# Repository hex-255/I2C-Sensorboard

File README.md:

# I2C-Sensorboard
Arduino Clone with multitude of I2C Sensors on-board meant as a learning platform for embedded programming

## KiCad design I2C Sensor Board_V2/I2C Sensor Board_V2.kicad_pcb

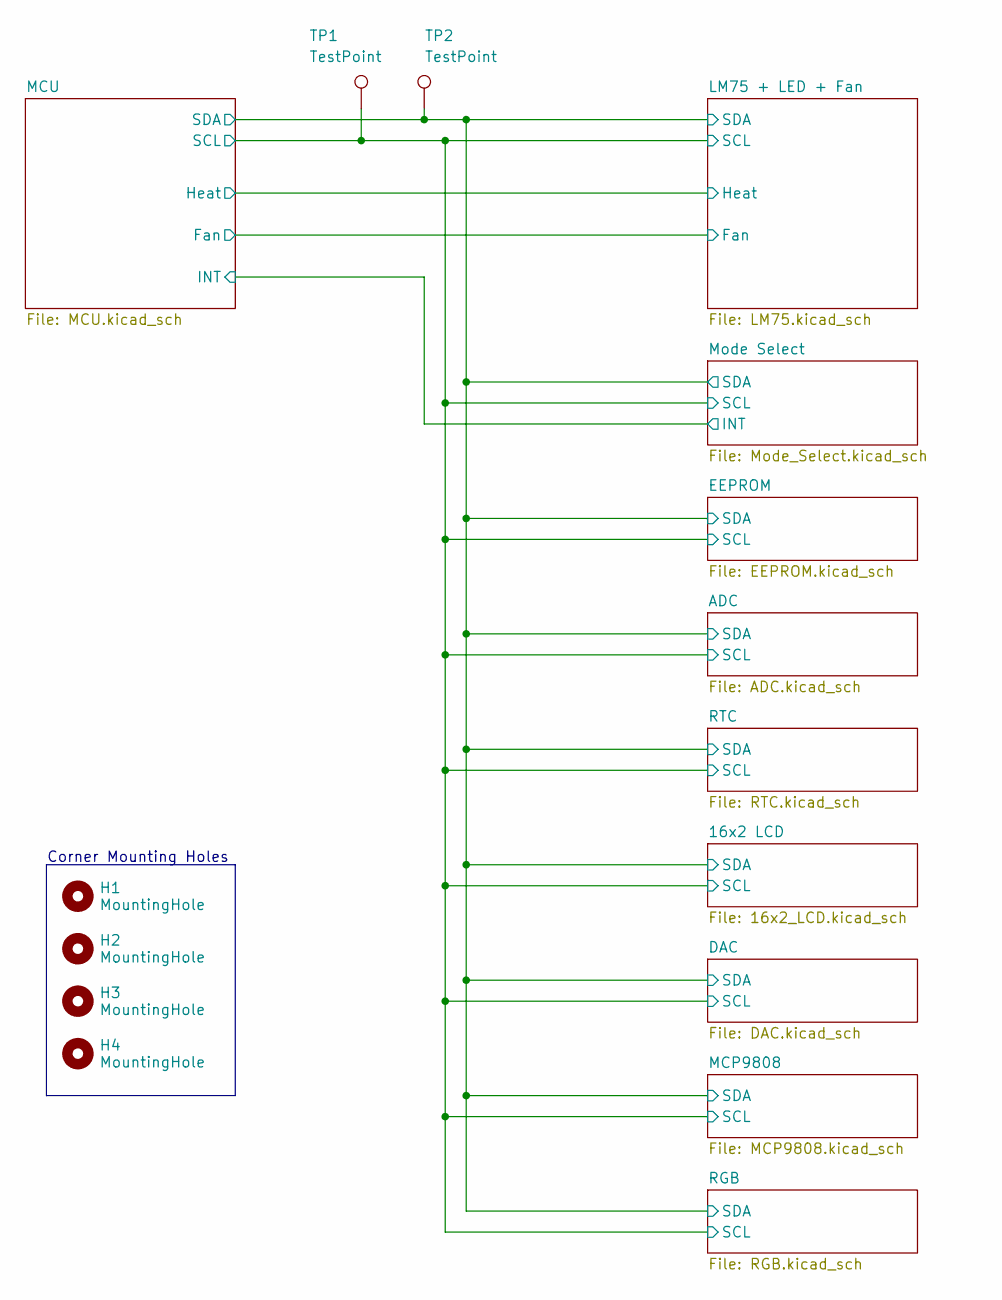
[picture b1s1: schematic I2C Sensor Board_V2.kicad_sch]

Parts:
H1, H2, H3, H4: MountingHole; MountingHole_3.2mm_M3_DIN965_Pad
TP1, TP2: TestPoint; Testpoint_5019_HandSolder

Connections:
/MCU/SCL: TP1.1 (1_1); also elsewhere on the board
/MCU/SDA: TP2.1 (1_1); also elsewhere on the board

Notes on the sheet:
Corner Mounting Holes

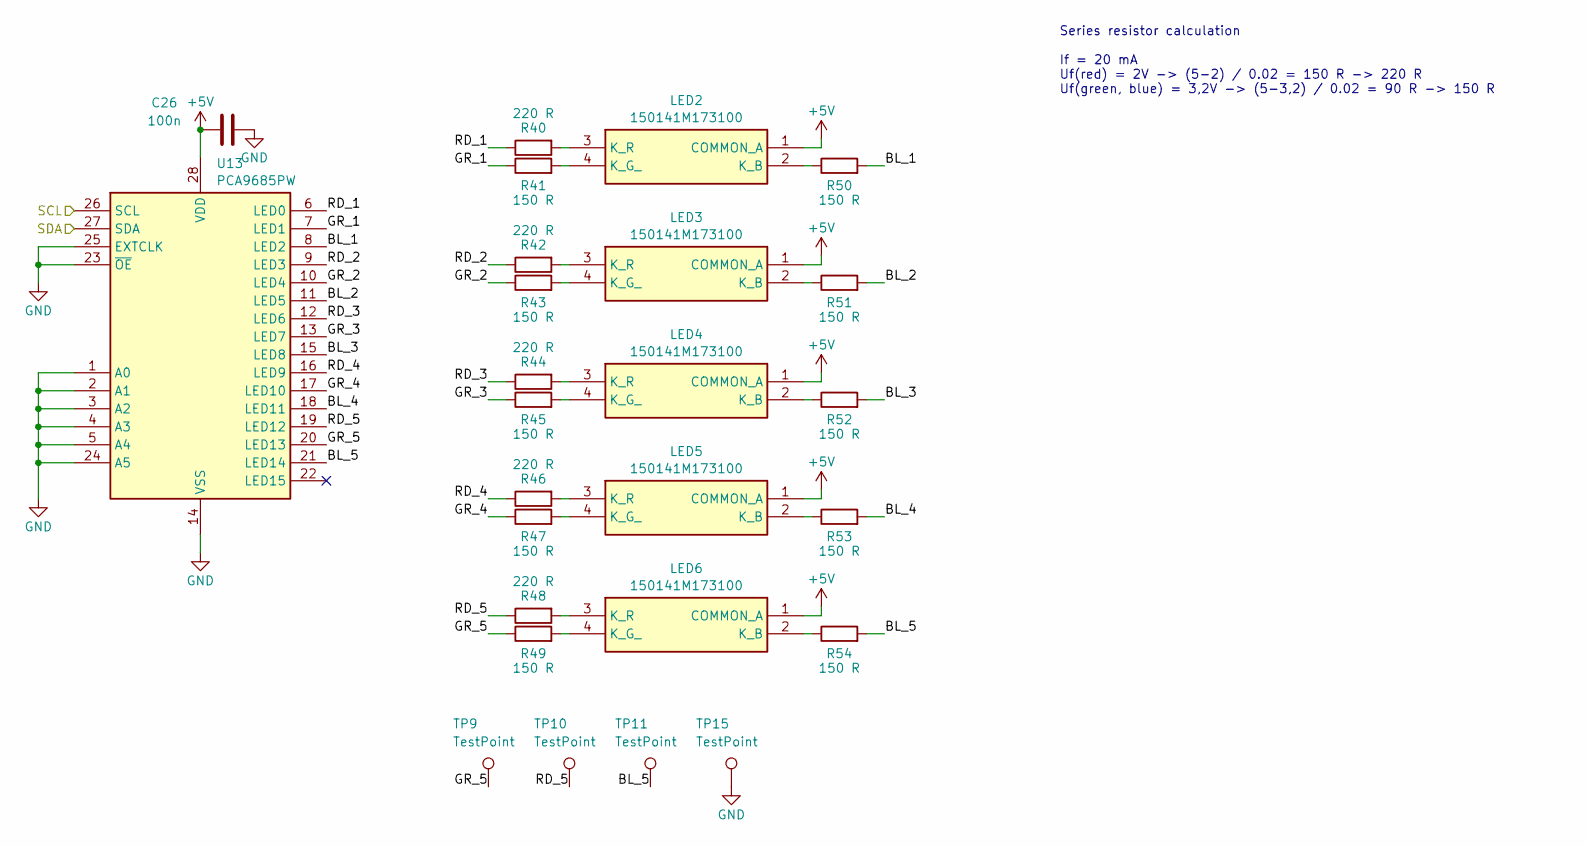
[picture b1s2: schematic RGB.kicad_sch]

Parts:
C26: 100n; C_0805_2012Metric_Pad1.18x1.45mm_HandSolder
LED2, LED3, LED4, LED5, LED6: 150141M173100; Manufacturer_Part_Number 150141M173100; Mouser Part Number 710-150141M173100
R40, R42, R44, R46, R48: 220 R; R_0805_2012Metric_Pad1.20x1.40mm_HandSolder
R41, R43, R45, R47, R49, R50, R51, R52, R53, R54: 150 R; R_0805_2012Metric_Pad1.20x1.40mm_HandSolder
TP9, TP10, TP11, TP15: TestPoint; Testpoint_5019_HandSolder
U13: PCA9685PW; TSSOP-28_4.4x9.7mm_P0.65mm

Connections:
+5V: C26.1, LED2.1 (COMMON_A), LED3.1 (COMMON_A), LED4.1 (COMMON_A), LED5.1 (COMMON_A), LED6.1 (COMMON_A), U13.28 (VDD); also elsewhere on the board
/MCU/SCL: U13.26 (SCL); also elsewhere on the board
/MCU/SDA: U13.27 (SDA); also elsewhere on the board
/RGB/BL_1: R50.2, U13.8 (LED2)
/RGB/BL_2: R51.2, U13.11 (LED5)
/RGB/BL_3: R52.2, U13.15 (LED8)
/RGB/BL_4: R53.2, U13.18 (LED11)
/RGB/BL_5: R54.2, TP11.1 (1_1), U13.21 (LED14)
/RGB/GR_1: R41.1, U13.7 (LED1)
/RGB/GR_2: R43.1, U13.10 (LED4)
/RGB/GR_3: R45.1, U13.13 (LED7)
/RGB/GR_4: R47.1, U13.17 (LED10)
/RGB/GR_5: R49.1, TP9.1 (1_1), U13.20 (LED13)
/RGB/RD_1: R40.1, U13.6 (LED0)
/RGB/RD_2: R42.1, U13.9 (LED3)
/RGB/RD_3: R44.1, U13.12 (LED6)
/RGB/RD_4: R46.1, U13.16 (LED9)
/RGB/RD_5: R48.1, TP10.1 (1_1), U13.19 (LED12)
GND: C26.2, TP15.1, U13.1 (A0), U13.2 (A1), U13.3 (A2), U13.4 (A3), U13.5 (A4), U13.14 (VSS), U13.23 (~OE), U13.24 (A5), U13.25 (EXTCLK); also elsewhere on the board
unnamed: LED2.2 (K_B), R50.1
unnamed: LED2.4 (K_G_), R41.2
unnamed: LED2.3 (K_R), R40.2
unnamed: LED3.2 (K_B), R51.1
unnamed: LED3.4 (K_G_), R43.2
unnamed: LED3.3 (K_R), R42.2
unnamed: LED4.2 (K_B), R52.1
unnamed: LED4.4 (K_G_), R45.2
unnamed: LED4.3 (K_R), R44.2
unnamed: LED5.2 (K_B), R53.1
unnamed: LED5.4 (K_G_), R47.2
unnamed: LED5.3 (K_R), R46.2
unnamed: LED6.2 (K_B), R54.1
unnamed: LED6.4 (K_G_), R49.2
unnamed: LED6.3 (K_R), R48.2

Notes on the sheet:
Series resistor calculation If = 20 mA Uf(red) = 2V -> (5-2) / 0.02 = 150 R -> 220 R Uf(green, blue) = 3,2V -> (5-3,2) / 0.02 = 90 R -> 150 R

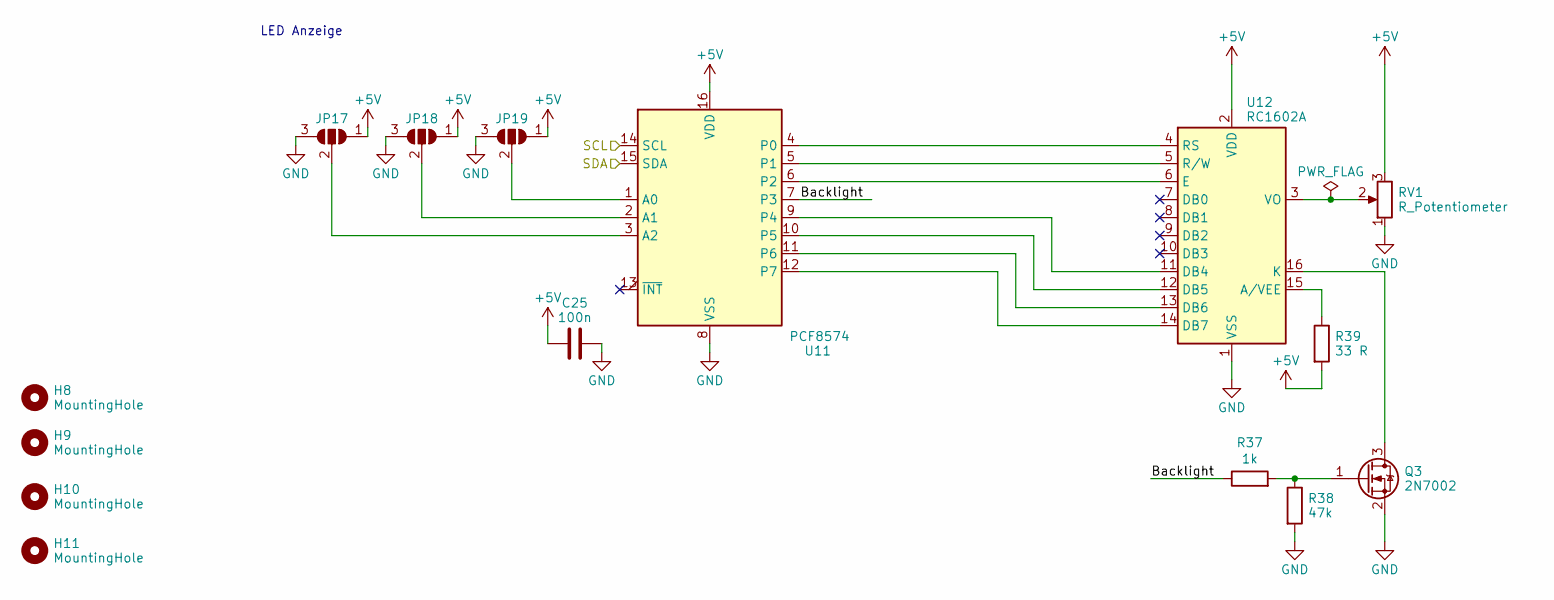
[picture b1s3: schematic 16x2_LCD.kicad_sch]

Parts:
C25: 100n; C_0805_2012Metric_Pad1.18x1.45mm_HandSolder
H8, H9, H10, H11: MountingHole; MountingHole_3.2mm_M3_DIN965_Pad
JP17, JP18, JP19: SolderJumper_3_Open; SolderJumper-3_P1.3mm_Open_Pad1.0x1.5mm_NumberLabels
Q3: 2N7002; SOT-23
R37: 1k; R_0805_2012Metric_Pad1.20x1.40mm_HandSolder
R38: 47k; R_0805_2012Metric_Pad1.20x1.40mm_HandSolder
R39: 33 R; R_0805_2012Metric_Pad1.20x1.40mm_HandSolder
RV1: R_Potentiometer; TRIM_TC33X-2-103E
U11: PCF8574; SOIC-16W_7.5x10.3mm_P1.27mm
U12: RC1602A; PinSocket_1x16_P2.54mm_Vertical

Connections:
+5V: C25.1, JP17.1 (A), JP18.1 (A), JP19.1 (A), R39.2, RV1.3, U11.16 (VDD), U12.2 (VDD); also elsewhere on the board
/16x2 LCD/Backlight: R37.1, U11.7 (P3)
/MCU/SCL: U11.14 (SCL); also elsewhere on the board
/MCU/SDA: U11.15 (SDA); also elsewhere on the board
GND: C25.2, JP17.3 (B), JP18.3 (B), JP19.3 (B), Q3.2 (S), R38.2, RV1.1, U11.8 (VSS), U12.1 (VSS); also elsewhere on the board
unnamed: JP17.2 (C), U11.3 (A2)
unnamed: JP18.2 (C), U11.2 (A1)
unnamed: JP19.2 (C), U11.1 (A0)
unnamed: Q3.3 (D), U12.16 (K)
unnamed: Q3.1 (G), R37.2, R38.1
unnamed: U11.4 (P0), U12.4 (RS)
unnamed: U11.5 (P1), U12.5 (R/W)
unnamed: U11.6 (P2), U12.6 (E)
unnamed: U11.9 (P4), U12.11 (DB4)
unnamed: U11.10 (P5), U12.12 (DB5)
unnamed: U11.11 (P6), U12.13 (DB6)
unnamed: U11.12 (P7), U12.14 (DB7)
unnamed: R39.1, U12.15 (A/VEE)
unnamed: RV1.2, U12.3 (VO)

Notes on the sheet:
LED Anzeige

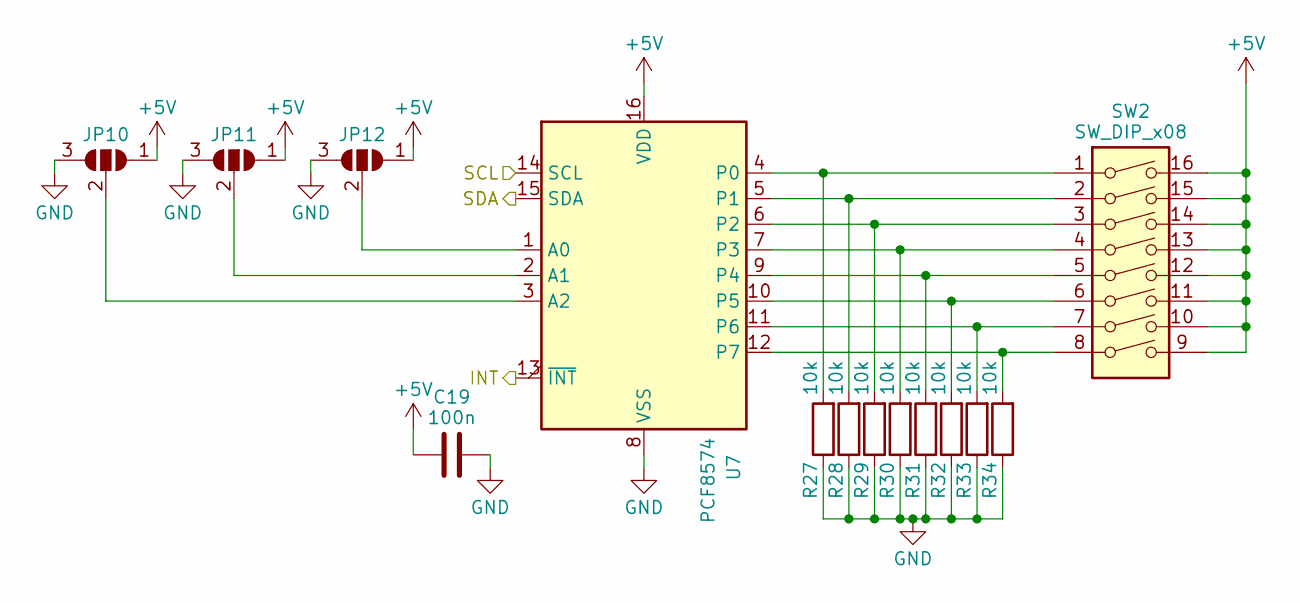
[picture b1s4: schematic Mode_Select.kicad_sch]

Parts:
C19: 100n; C_0805_2012Metric_Pad1.18x1.45mm_HandSolder
JP10, JP11, JP12: SolderJumper_3_Open; SolderJumper-3_P1.3mm_Open_Pad1.0x1.5mm_NumberLabels
R27, R28, R29, R30, R31, R32, R33, R34: 10k; R_0805_2012Metric_Pad1.20x1.40mm_HandSolder
SW2: SW_DIP_x08; SW_DIP_SPSTx08_Slide_9.78x22.5mm_W8.61mm_P2.54mm
U7: PCF8574; SOIC-16W_7.5x10.3mm_P1.27mm

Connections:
+5V: C19.1, JP10.1 (A), JP11.1 (A), JP12.1 (A), SW2.9, SW2.10, SW2.11, SW2.12, SW2.13, SW2.14, SW2.15, SW2.16, U7.16 (VDD); also elsewhere on the board
/MCU/INT: U7.13 (~INT); also elsewhere on the board
/MCU/SCL: U7.14 (SCL); also elsewhere on the board
/MCU/SDA: U7.15 (SDA); also elsewhere on the board
GND: C19.2, JP10.3 (B), JP11.3 (B), JP12.3 (B), R27.1, R28.1, R29.1, R30.1, R31.1, R32.1, R33.1, R34.1, U7.8 (VSS); also elsewhere on the board
unnamed: JP10.2 (C), U7.3 (A2)
unnamed: JP11.2 (C), U7.2 (A1)
unnamed: JP12.2 (C), U7.1 (A0)
unnamed: R27.2, SW2.1, U7.4 (P0)
unnamed: R28.2, SW2.2, U7.5 (P1)
unnamed: R29.2, SW2.3, U7.6 (P2)
unnamed: R30.2, SW2.4, U7.7 (P3)
unnamed: R31.2, SW2.5, U7.9 (P4)
unnamed: R32.2, SW2.6, U7.10 (P5)
unnamed: R33.2, SW2.7, U7.11 (P6)
unnamed: R34.2, SW2.8, U7.12 (P7)

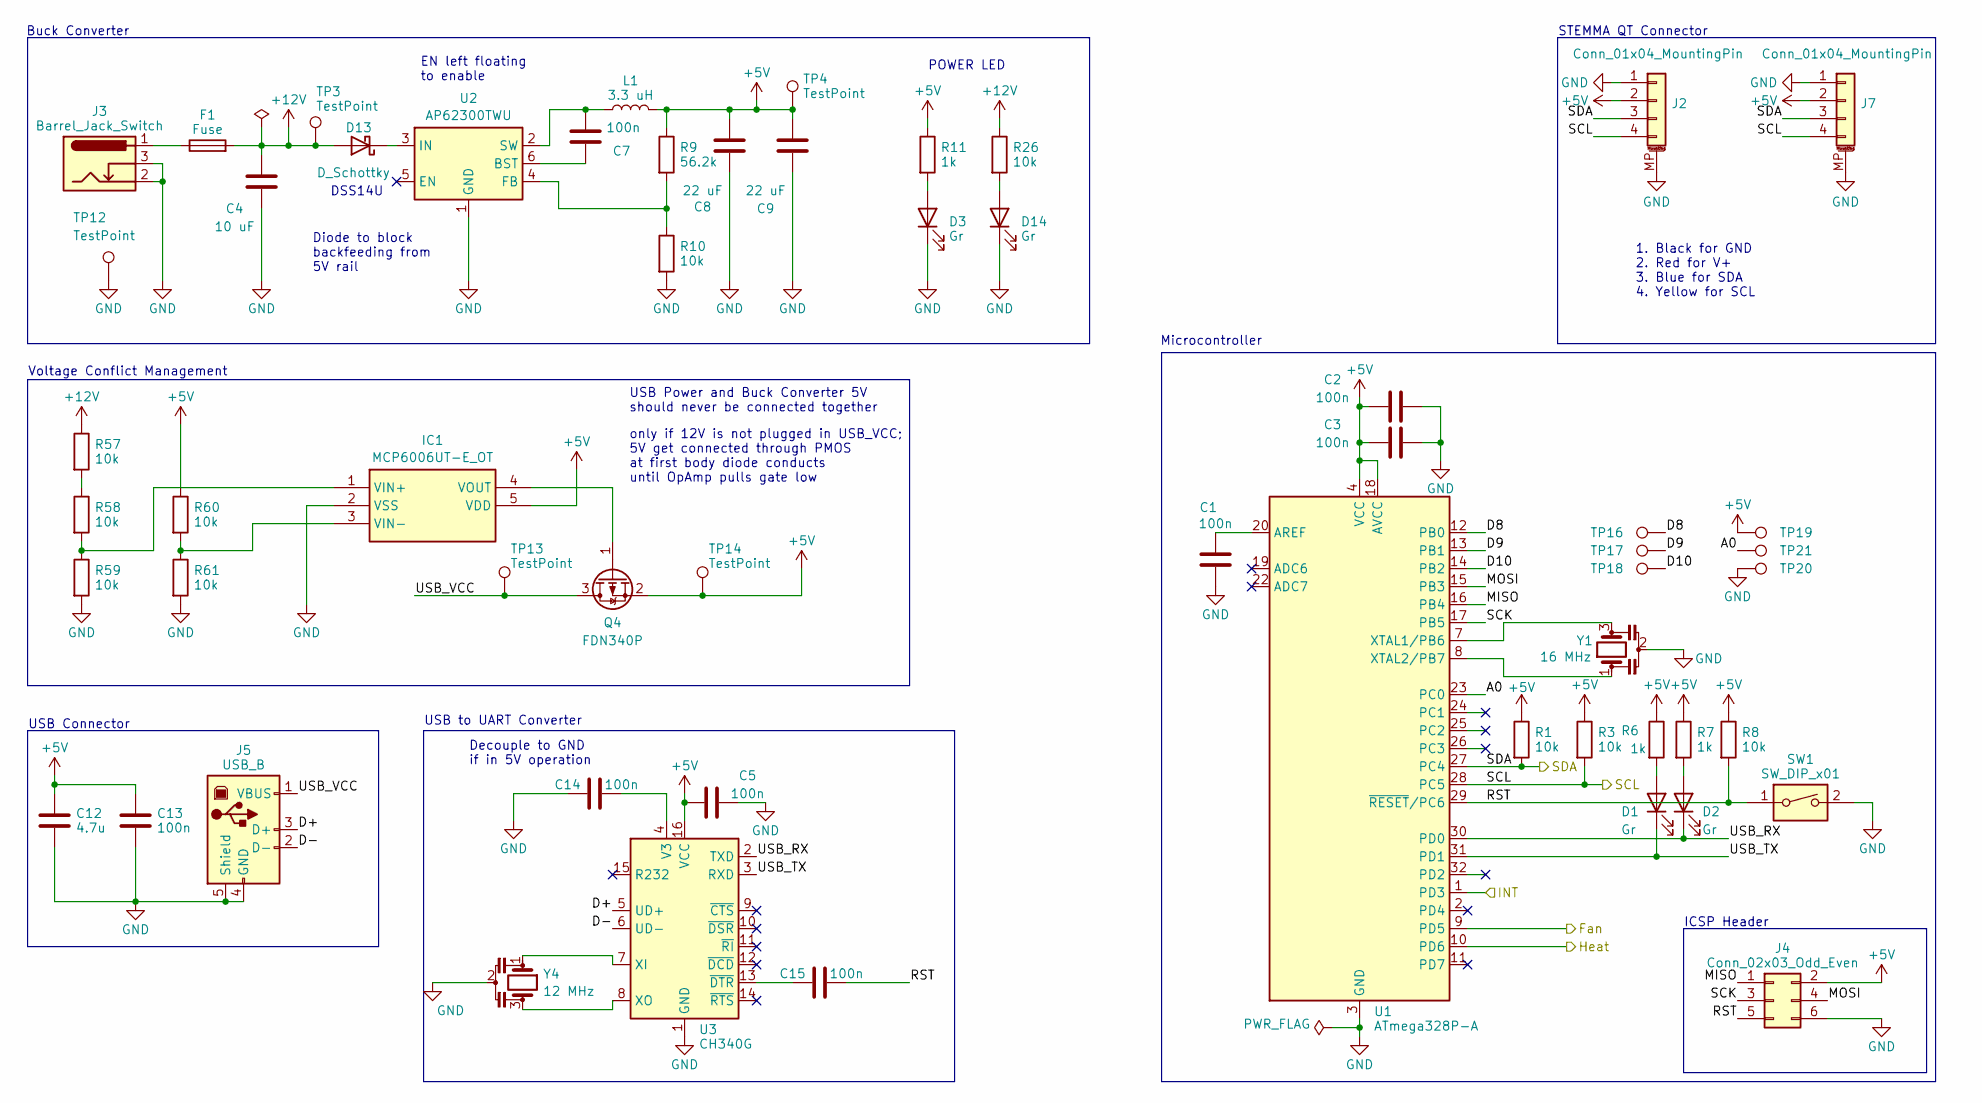
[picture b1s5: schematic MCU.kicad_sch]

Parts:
C1, C2, C3, C5, C7, C13, C14, C15: 100n; C_0805_2012Metric_Pad1.18x1.45mm_HandSolder
C4: 10 uF; C_1206_3216Metric_Pad1.33x1.80mm_HandSolder
C8, C9: 22 uF; C_1206_3216Metric_Pad1.33x1.80mm_HandSolder
C12: 4.7u; C_0805_2012Metric_Pad1.18x1.45mm_HandSolder
D1, D2, D3, D14: Gr; LED_0805_2012Metric_Pad1.15x1.40mm_HandSolder
D13: D_Schottky; D_SOD-123F
F1: Fuse; 154005DR
IC1: MCP6006UT-E_OT; SOT95P280X145-5N; Manufacturer_Part_Number MCP6006UT-E/OT; Mouser Part Number 579-MCP6006UT-E/OT
J2, J7: Conn_01x04_MountingPin; JST_SH_SM04B-SRSS-TB_1x04-1MP_P1.00mm_Horizontal
J3: Barrel_Jack_Switch; BarrelJack_Horizontal
J4: Conn_02x03_Odd_Even; PinHeader_2x03_P2.54mm_Vertical
J5: USB_B; USB_B_OST_USB-B1HSxx_Horizontal
L1: 3.3 uH; IND_WE-HEPC_5030_WRE
Q4: FDN340P; SOT-23
R1, R3, R8, R10, R26, R57, R58, R59, R60, R61: 10k; R_0805_2012Metric_Pad1.20x1.40mm_HandSolder
R6, R7, R11: 1k; R_0805_2012Metric_Pad1.20x1.40mm_HandSolder
R9: 56.2k; R_0805_2012Metric_Pad1.20x1.40mm_HandSolder
SW1: SW_DIP_x01; SW_Push_1P1T_NO_CK_KMR2
TP3, TP4, TP12, TP13, TP14: TestPoint; Testpoint_5019_HandSolder
TP16, TP17, TP18, TP19, TP20, TP21: TestPoint; TestPoint_THTPad_D1.5mm_Drill0.7mm
U1: ATmega328P-A; TQFP-32_7x7mm_P0.8mm
U2: AP62300TWU; TSOT-23-6
U3: CH340G; SOIC-16_3.9x9.9mm_P1.27mm
Y1: 16 MHz; OSC_CSTNE12M0G550000R0
Y4: 12 MHz; OSC_CSTNE12M0G550000R0

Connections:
+5V: C2.1, C3.1, C5.1, C8.2, C9.2, C12.2, C13.2, IC1.5 (VDD), J2.2, J4.2, J7.2, L1.2, Q4.2 (S), R1.1, R3.1, R6.1, R7.1, R8.1, R9.1, R11.1, R60.1, TP4.1 (1_1), TP14.1 (1_1), TP19.1 (1_1), U1.4 (VCC), U1.6 (VCC), U1.18 (AVCC), U3.16 (VCC); also elsewhere on the board
+12V: C4.2, D13.2 (A), F1.2, R26.1, R57.1, TP3.1 (1_1); also elsewhere on the board
/LM75 + LED + Fan/Fan: U1.9 (PD5); also elsewhere on the board
/LM75 + LED + Fan/Heat: U1.10 (PD6); also elsewhere on the board
/MCU/A0: TP21.1 (1_1), U1.23 (PC0)
/MCU/D8: TP16.1 (1_1), U1.12 (PB0)
/MCU/D9: TP17.1 (1_1), U1.13 (PB1)
/MCU/D10: TP18.1 (1_1), U1.14 (PB2)
/MCU/D+: J5.3 (D+), U3.5 (UD+)
/MCU/D-: J5.2 (D-), U3.6 (UD-)
/MCU/INT: U1.1 (PD3); also elsewhere on the board
/MCU/MISO: J4.1, U1.16 (PB4)
/MCU/MOSI: J4.4, U1.15 (PB3)
/MCU/RST: C15.2, J4.5, R8.2, SW1.1, U1.29 (~RESET/PC6)
/MCU/SCK: J4.3, U1.17 (PB5)
/MCU/SCL: J2.4, J7.4, R3.2, U1.28 (PC5); also elsewhere on the board
/MCU/SDA: J2.3, J7.3, R1.2, U1.27 (PC4); also elsewhere on the board
/MCU/USB_RX: D2.1 (K), U1.30 (PD0), U3.2 (TXD)
/MCU/USB_TX: D1.1 (K), U1.31 (PD1), U3.3 (RXD)
/MCU/USB_VCC: J5.1 (VBUS), Q4.3 (D), TP13.1 (1_1)
GND: C1.1, C2.2, C3.2, C4.1, C5.2, C8.1, C9.1, C12.1, C13.1, C14.1, D3.1 (K), D14.1 (K), IC1.2 (VSS), J2.1, J2.MP (MountPin), J3.2, J3.3, J4.6, J5.4 (GND), J5.5 (Shield), J7.1, J7.MP (MountPin), R10.2, R59.2, R61.2, SW1.2, TP12.1 (1_1), TP20.1 (1_1), U1.3 (GND), U1.5 (GND), U1.21 (GND), U2.1 (GND), U3.1 (GND), Y1.2, Y4.2; also elsewhere on the board
unnamed: D1.2 (A), R6.2
unnamed: D2.2 (A), R7.2
unnamed: D3.2 (A), R11.2
unnamed: D13.1 (K), U2.3 (IN)
unnamed: D14.2 (A), R26.2
unnamed: F1.1, J3.1
unnamed: IC1.1 (VIN+), R58.2, R59.1
unnamed: IC1.3 (VIN-), R60.2, R61.1
unnamed: IC1.4 (VOUT), Q4.1 (G)
unnamed: R57.2, R58.1
unnamed: C1.2, U1.20 (AREF)
unnamed: U1.7 (XTAL1/PB6), Y1.3
unnamed: U1.8 (XTAL2/PB7), Y1.1
unnamed: C7.1, U2.6 (BST)
unnamed: R9.2, R10.1, U2.4 (FB)
unnamed: C7.2, L1.1, U2.2 (SW)
unnamed: C14.2, U3.4 (V3)
unnamed: U3.7 (XI), Y4.1
unnamed: U3.8 (XO), Y4.3
unnamed: C15.1, U3.13 (~DTR)

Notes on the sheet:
USB Connector
Microcontroller
USB to UART Converter
Voltage Conflict Management
POWER LED
DSS14U
1. Black for GND 2. Red for V+ 3. Blue for SDA 4. Yellow for SCL
USB Power and Buck Converter 5V should never be connected together
ICSP Header
STEMMA QT Connector
Decouple to GND if in 5V operation
Diode to block backfeeding from 5V rail
Buck Converter
only if 12V is not plugged in USB_VCC; 5V get connected through PMOS at first body diode conducts until OpAmp pulls gate low
EN left floating to enable

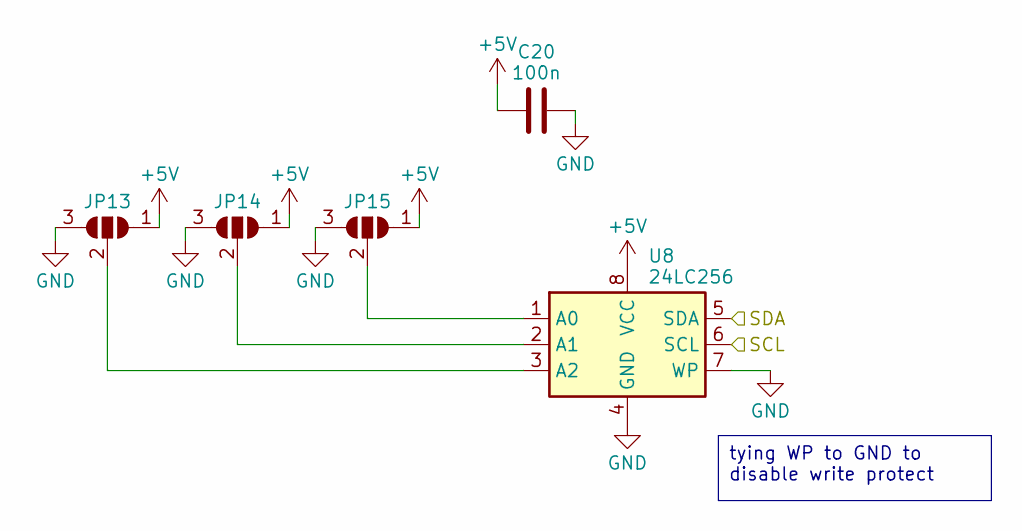
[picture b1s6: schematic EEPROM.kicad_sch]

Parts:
C20: 100n; C_0805_2012Metric_Pad1.18x1.45mm_HandSolder
JP13, JP14, JP15: SolderJumper_3_Open; SolderJumper-3_P1.3mm_Open_Pad1.0x1.5mm_NumberLabels
U8: 24LC256; MSOP-8_3x3mm_P0.65mm

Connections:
+5V: C20.1, JP13.1 (A), JP14.1 (A), JP15.1 (A), U8.8 (VCC); also elsewhere on the board
/MCU/SCL: U8.6 (SCL); also elsewhere on the board
/MCU/SDA: U8.5 (SDA); also elsewhere on the board
GND: C20.2, JP13.3 (B), JP14.3 (B), JP15.3 (B), U8.4 (GND), U8.7 (WP); also elsewhere on the board
unnamed: JP13.2 (C), U8.3 (A2)
unnamed: JP14.2 (C), U8.2 (A1)
unnamed: JP15.2 (C), U8.1 (A0)

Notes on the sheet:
tying WP to GND to disable write protect

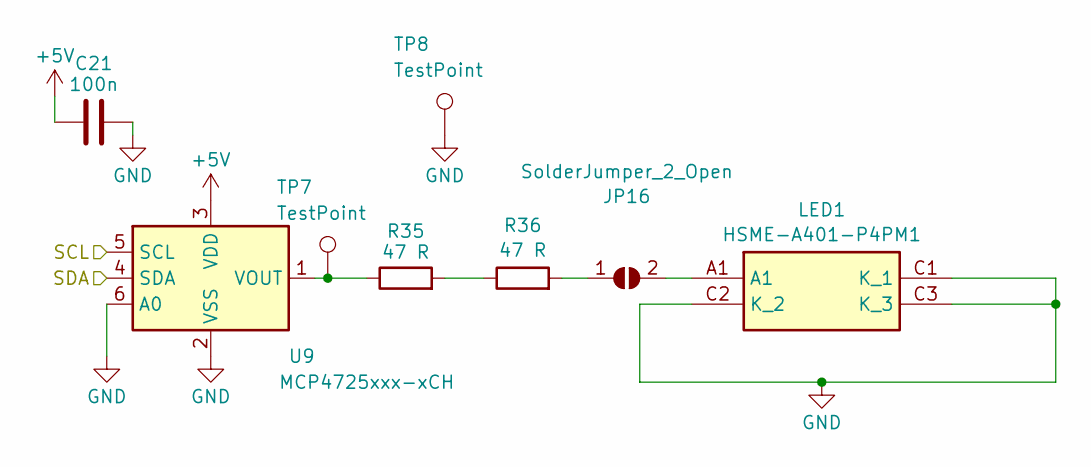
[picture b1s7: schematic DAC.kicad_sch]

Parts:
C21: 100n; C_0805_2012Metric_Pad1.18x1.45mm_HandSolder
JP16: SolderJumper_2_Open; SolderJumper-2_P1.3mm_Open_TrianglePad1.0x1.5mm
LED1: HSME-A401-P4PM1; HSMEA401P4PM1; Manufacturer_Part_Number HSME-A401-P4PM1; Mouser Part Number 630-HSME-A401-P4PM1
R35, R36: 47 R; R_0805_2012Metric_Pad1.20x1.40mm_HandSolder
TP7, TP8: TestPoint; Testpoint_5019_HandSolder
U9: MCP4725xxx-xCH; SOT-23-6

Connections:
+5V: C21.1, U9.3 (VDD); also elsewhere on the board
/MCU/SCL: U9.5 (SCL); also elsewhere on the board
/MCU/SDA: U9.4 (SDA); also elsewhere on the board
GND: C21.2, LED1.C1 (K_1), LED1.C2 (K_2), LED1.C3 (K_3), TP8.1 (1_1), U9.2 (VSS), U9.6 (A0); also elsewhere on the board
unnamed: JP16.1 (A), R36.2
unnamed: JP16.2 (B), LED1.A1
unnamed: R35.2, R36.1
unnamed: R35.1, TP7.1 (1_1), U9.1 (VOUT)

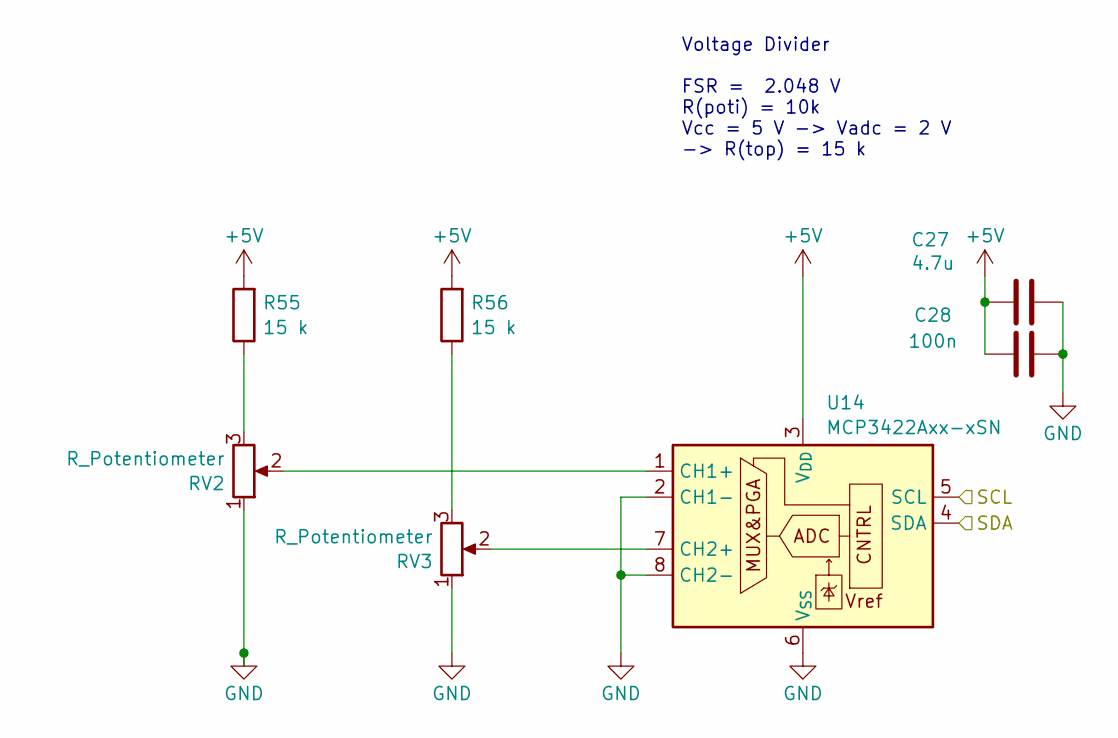
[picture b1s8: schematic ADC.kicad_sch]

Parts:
C27: 4.7u; C_0805_2012Metric_Pad1.18x1.45mm_HandSolder
C28: 100n; C_0805_2012Metric_Pad1.18x1.45mm_HandSolder
R55, R56: 15 k; R_0805_2012Metric_Pad1.20x1.40mm_HandSolder
RV2, RV3: R_Potentiometer; Piher_N6L50T8S
U14: MCP3422Axx-xSN; SOIC-8_3.9x4.9mm_P1.27mm

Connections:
+5V: C27.2, C28.1, R55.2, R56.2, U14.3 (V_{DD}); also elsewhere on the board
/MCU/SCL: U14.5 (SCL); also elsewhere on the board
/MCU/SDA: U14.4 (SDA); also elsewhere on the board
GND: C27.1, C28.2, RV2.1, RV3.1, U14.2 (CH1-), U14.6 (V_{SS}), U14.8 (CH2-); also elsewhere on the board
unnamed: R55.1, RV2.3
unnamed: R56.1, RV3.3
unnamed: RV2.2, U14.1 (CH1+)
unnamed: RV3.2, U14.7 (CH2+)

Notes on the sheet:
Voltage Divider FSR = 2.048 V R(poti) = 10k Vcc = 5 V -> Vadc = 2 V -> R(top) = 15 k

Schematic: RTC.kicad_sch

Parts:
BT1: Battery_Cell; BAT_BC-2003
C22: 100n; C_0805_2012Metric_Pad1.18x1.45mm_HandSolder
C23, C24: 7p; C_0805_2012Metric_Pad1.18x1.45mm_HandSolder
U10: MCP7940N-xSN; SOIC-8_3.9x4.9mm_P1.27mm
Y3: Crystal; Crystal_Round_D2.0mm_Vertical

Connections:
+5V: C22.1, U10.8 (VCC); also elsewhere on the board
/MCU/SCL: U10.6 (SCL); also elsewhere on the board
/MCU/SDA: U10.5 (SDA); also elsewhere on the board
GND: BT1.2 (-), C22.2, C23.2, C24.2, U10.4 (VSS); also elsewhere on the board
unnamed: BT1.1 (+), U10.3 (VBAT)
unnamed: C23.1, U10.1 (X1), Y3.2
unnamed: C24.1, U10.2 (X2), Y3.1

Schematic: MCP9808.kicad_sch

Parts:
C18: 100n; C_0805_2012Metric_Pad1.18x1.45mm_HandSolder
JP7, JP8, JP9: SolderJumper_3_Open; SolderJumper-3_P1.3mm_Open_Pad1.0x1.5mm_NumberLabels
U6: MCP9808_MSOP; MSOP-8_3x3mm_P0.65mm

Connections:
+5V: C18.1, JP7.1 (A), JP8.1 (A), JP9.1 (A), U6.8 (V_{DD}); also elsewhere on the board
/MCU/SCL: U6.2 (SCL); also elsewhere on the board
/MCU/SDA: U6.1 (SDA); also elsewhere on the board
GND: C18.2, JP7.3 (B), JP8.3 (B), JP9.3 (B), U6.4 (GND); also elsewhere on the board
unnamed: JP7.2 (C), U6.5 (A2)
unnamed: JP8.2 (C), U6.6 (A1)
unnamed: JP9.2 (C), U6.7 (A0)

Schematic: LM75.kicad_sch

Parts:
C6, C10: 100n; C_0805_2012Metric_Pad1.18x1.45mm_HandSolder
D4, D11, D12: R; LED_0805_2012Metric_Pad1.15x1.40mm_HandSolder
D5, D6, D7, D8: Gr; LED_0805_2012Metric_Pad1.15x1.40mm_HandSolder
D9, D10: Yl; LED_0805_2012Metric_Pad1.15x1.40mm_HandSolder
H5, H6, H7: MountingHole; MountingHole_3.2mm_M3_DIN965_Pad
J6: Conn_01x02_Pin; PinHeader_1x02_P2.54mm_Vertical
JP1, JP2, JP3, JP4, JP5, JP6: SolderJumper_3_Open; SolderJumper-3_P1.3mm_Open_Pad1.0x1.5mm_NumberLabels
Q1, Q2: 2N7002; SOT-23
R2: 200k; R_0805_2012Metric_Pad1.20x1.40mm_HandSolder
R12, R14, R15, R16, R17, R20, R21, R22, R23, R24, R25: 1k; R_0805_2012Metric_Pad1.20x1.40mm_HandSolder
R13: 220 1W; R_Axial_DIN0204_L3.6mm_D1.6mm_P12.70mm_Horizontal
R18, R19: 47k; R_0805_2012Metric_Pad1.20x1.40mm_HandSolder
TP5, TP6: TestPoint; Testpoint_5019_HandSolder
U4: LM75B; SOIC-8_3.9x4.9mm_P1.27mm
U5: PCF8574; SOIC-16W_7.5x10.3mm_P1.27mm

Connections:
+5V: C6.1, C10.1, D7.2 (A), D8.2 (A), D9.2 (A), D10.2 (A), D11.2 (A), D12.2 (A), JP1.1 (A), JP2.1 (A), JP3.1 (A), JP4.1 (A), JP5.1 (A), JP6.1 (A), R2.1, R12.1, U4.8 (+Vs), U5.16 (VDD); also elsewhere on the board
+12V: J6.2, R13.2, TP6.1 (1_1); also elsewhere on the board
/LM75 + LED + Fan/Fan: R16.1, R17.1; also elsewhere on the board
/LM75 + LED + Fan/Heat: R14.1, R15.1; also elsewhere on the board
/MCU/SCL: U4.2 (SCL), U5.14 (SCL); also elsewhere on the board
/MCU/SDA: U4.1 (SDA), U5.15 (SDA); also elsewhere on the board
GND: C6.2, C10.2, D5.1 (K), D6.1 (K), JP1.3 (B), JP2.3 (B), JP3.3 (B), JP4.3 (B), JP5.3 (B), JP6.3 (B), Q1.2 (S), Q2.2 (S), R18.2, R19.2, U4.4 (GND), U5.8 (VSS); also elsewhere on the board
unnamed: D4.2 (A), R12.2
unnamed: D4.1 (K), R2.2, U4.3 (O.S.)
unnamed: D5.2 (A), R14.2
unnamed: D6.2 (A), R16.2
unnamed: D7.1 (K), R20.2
unnamed: D8.1 (K), R21.2
unnamed: D9.1 (K), R22.2
unnamed: D10.1 (K), R23.2
unnamed: D11.1 (K), R24.2
unnamed: D12.1 (K), R25.2
unnamed: J6.1, Q2.3 (D)
unnamed: JP1.2 (C), U4.7 (A0)
unnamed: JP2.2 (C), U4.6 (A1)
unnamed: JP3.2 (C), U4.5 (A2)
unnamed: JP4.2 (C), U5.3 (A2)
unnamed: JP5.2 (C), U5.2 (A1)
unnamed: JP6.2 (C), U5.1 (A0)
unnamed: Q1.3 (D), R13.1, TP5.1 (1_1)
unnamed: Q1.1 (G), R15.2, R18.1
unnamed: Q2.1 (G), R17.2, R19.1
unnamed: R20.1, U5.4 (P0)
unnamed: R21.1, U5.5 (P1)
unnamed: R22.1, U5.6 (P2)
unnamed: R23.1, U5.7 (P3)
unnamed: R24.1, U5.9 (P4)
unnamed: R25.1, U5.10 (P5)

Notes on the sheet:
LM75
Lüfter
LED Anzeige
Heizwiderstand

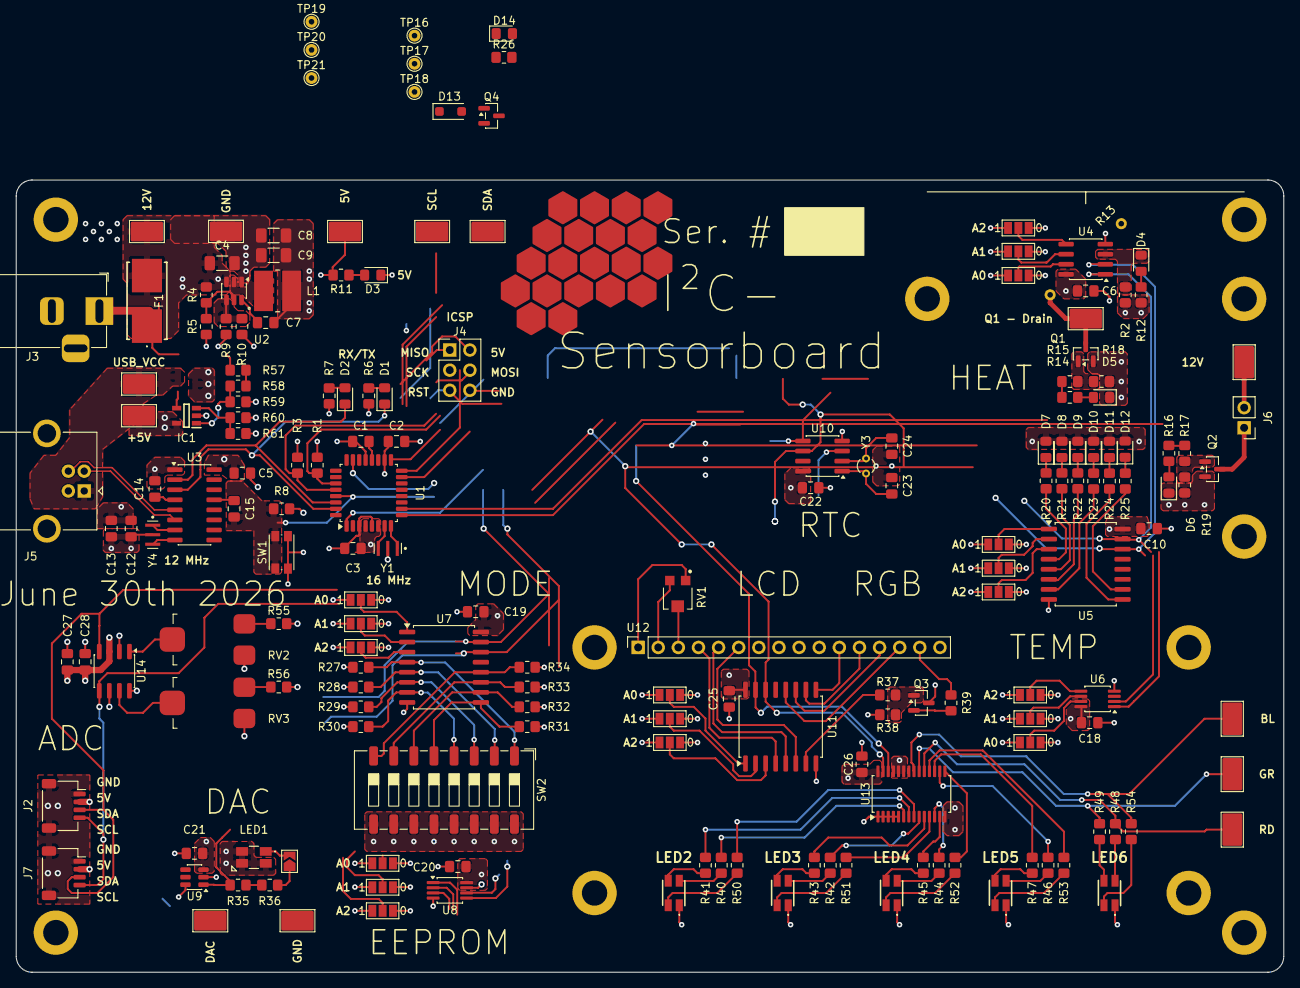
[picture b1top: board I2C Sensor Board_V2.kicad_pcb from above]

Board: 4 copper layers, 160.0 x 100.0 mm, 192 parts (1 on the bottom side), 141 nets.

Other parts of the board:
R4, R5: 10k; R_0805_2012Metric_Pad1.20x1.40mm_HandSolder

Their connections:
+12V: R4.1; also elsewhere on the board
GND: R5.2; also elsewhere on the board
unnamed: R4.2, R5.1
